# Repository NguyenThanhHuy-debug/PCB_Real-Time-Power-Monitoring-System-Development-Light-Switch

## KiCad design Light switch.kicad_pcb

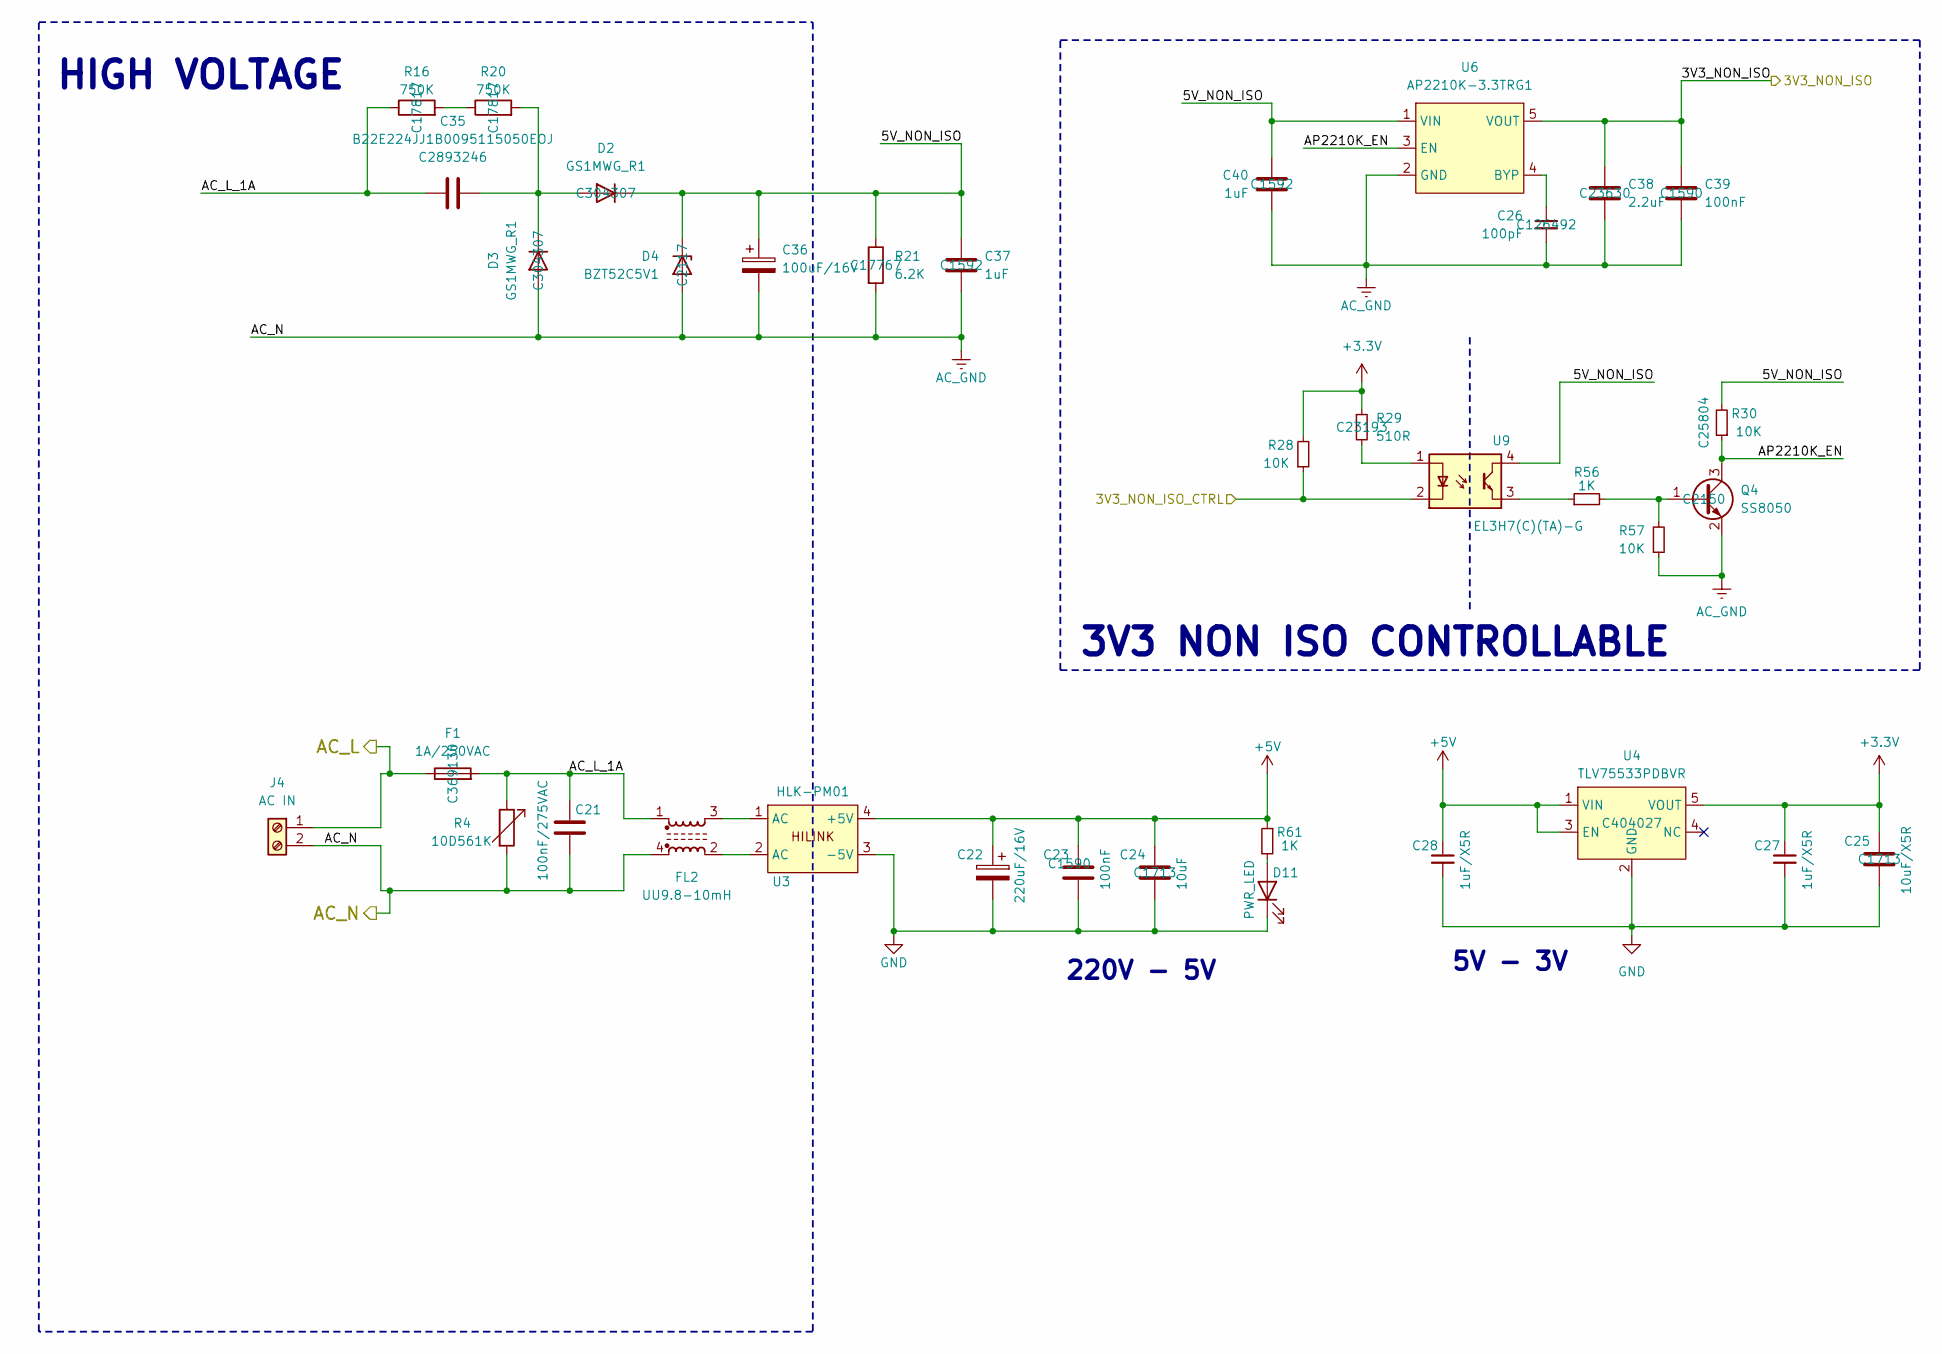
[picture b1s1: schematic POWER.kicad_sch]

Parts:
C21: 100nF/275VAC; C_Rect_L13.0mm_W6.0mm_P10.00mm_FKS3_FKP3_MKS4; JLC C489079
C22: 220uF/16V; C_Elec_6.3x7.7; JLC C3342
C23, C39: 100nF; C_0603_1608Metric; JLC C1590
C24: 10uF; C_0805_2012Metric; JLC C1713
C25: 10uF/X5R; C_0805_2012Metric; JLC C1713
C26: 100pF; C_0402_1005Metric; JLC C126492
C27, C28: 1uF/X5R; C_0603_1608Metric; JLC C15849
C35: B22E224JJ1B0095115050EOJ; C_Rect_L9.0mm_W5.1mm_P7.50mm_MKT; JLC C2893246
C36: 100uF/16V; CP_Radial_D5.0mm_P2.00mm; JLC C43803
C37, C40: 1uF; C_0603_1608Metric; JLC C1592
C38: 2.2uF; C_0603_1608Metric; JLC C23630
D2, D3: GS1MWG_R1; D_SMA; JLC C304307
D4: BZT52C5V1; D_SOD-123; JLC C2117
D11: PWR_LED; LED_0603_1608Metric; JLC C2286
F1: 1A/250VAC; JK250-120U_C369130; JLC C369130
FL2: UU9.8-10mH; JLC C148474
J4: AC IN; TerminalBlock_P5.00mm; JLC C3703
Q4: SS8050; SOT-23; JLC C2150
R4: 10D561K; MOV-10D561K_BRN; JLC C233178
R16, R20: 750K; R_0805_2012Metric; JLC C17817
R21: 6.2K; R_0805_2012Metric; JLC C17767
R28, R30, R57: 10K; R_0603_1608Metric; JLC C25804
R29: 510R; R_0603_1608Metric; JLC C23193
R56, R61: 1K; R_0603_1608Metric; JLC C21190
U3: HLK-PM01; CONV_HLK-PM01; JLC C209903
U4: TLV75533PDBVR; SOT-23-5; JLC C404027
U6: AP2210K-3.3TRG1; SOT-23-5; JLC C155508
U9: EL3H7(C)(TA)-G; SSOP-4_4.4x2.6mm_P1.27mm; JLC C92243

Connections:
+3.3V: C25.1, C27.1, R28.2, R29.1, U4.5 (VOUT); also elsewhere on the board
+5V: C22.1, C23.1, C24.1, C28.1, R61.1, U3.4 (+5V), U4.1 (VIN), U4.3 (EN); also elsewhere on the board
/AC_Peripheral/3V3_NON_ISO: C38.1, C39.1, U6.5 (VOUT); also elsewhere on the board
/AC_Peripheral/AC_L: F1.1, J4.1; also elsewhere on the board
/MCU/3V3_NON_ISO_CTRL: R28.1, U9.2 (K); also elsewhere on the board
/POWER/5V_NON_ISO: C36.1, C37.1, C40.1, D2.1 (K), D4.1 (K), R21.1, R30.2, U6.1 (VIN), U9.4 (E)
/POWER/AC_L_1A: C21.1, C35.1, F1.2, FL2.1, R4.1, R16.1
/POWER/AP2210K_EN: Q4.3 (C), R30.1, U6.3 (EN)
AC_GND: C21.2, C26.2, C36.2, C37.2, C38.2, C39.2, C40.2, D3.2 (A), D4.2 (A), FL2.4, J4.2, Q4.2 (E), R4.2, R21.2, R57.1, U6.2 (GND); also elsewhere on the board
GND: C22.2, C23.2, C24.2, C25.2, C27.2, C28.2, D11.1 (K), U3.3 (-5V), U4.2 (GND); also elsewhere on the board
unnamed: C35.2, D2.2 (A), D3.1 (K), R20.2
unnamed: D11.2 (A), R61.2
unnamed: FL2.2, U3.2 (AC)
unnamed: FL2.3, U3.1 (AC)
unnamed: Q4.1 (B), R56.2, R57.2
unnamed: R16.2, R20.1
unnamed: C26.1, U6.4 (BYP)
unnamed: R29.2, U9.1 (A)
unnamed: R56.1, U9.3 (C)

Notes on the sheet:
220V - 5V
3V3 NON ISO CONTROLLABLE
HIGH VOLTAGE
5V - 3V

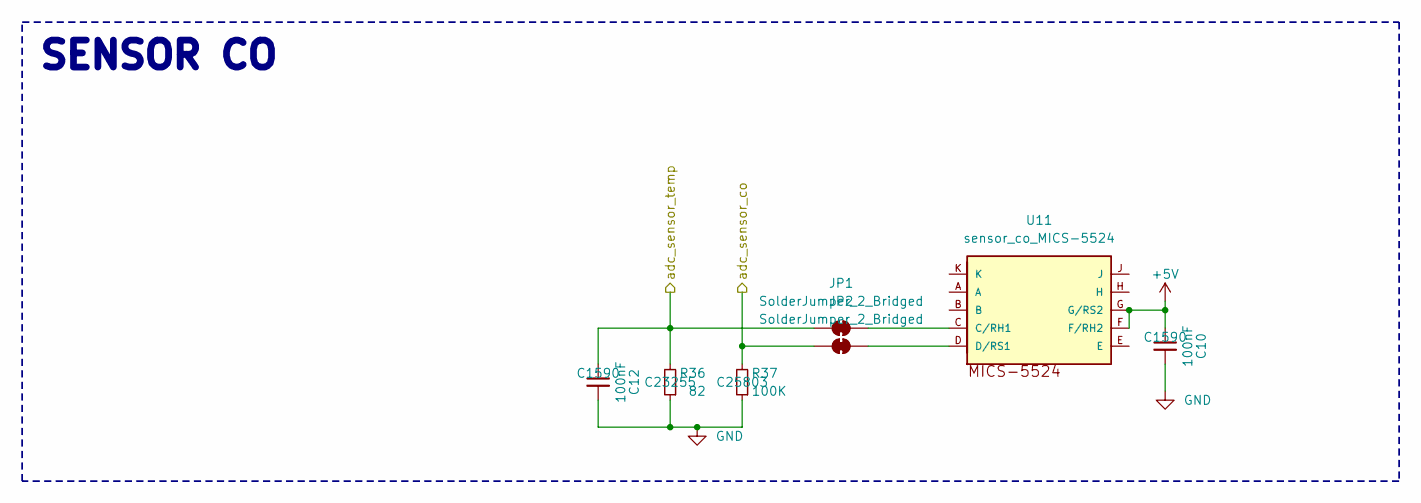
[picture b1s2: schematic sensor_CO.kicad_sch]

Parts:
C10, C12: 100nF; C_0603_1608Metric; JLC C1590
JP1, JP2: SolderJumper_2_Bridged; SolderJumper-2_P1.3mm_Bridged_RoundedPad1.0x1.5mm
R36: 82; R_0603_1608Metric; JLC C23255
R37: 100K; R_0603_1608Metric; JLC C25803
U11: sensor_co_MICS-5524; MICS-SMD10; JLC C3659348

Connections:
+5V: C10.1, U11.F (F/RH2), U11.G (G/RS2); also elsewhere on the board
/MCU/ADC1_INT10: JP2.1 (A), R37.2; also elsewhere on the board
/MCU/ADC1_INT11: C12.1, JP1.1 (A), R36.2; also elsewhere on the board
GND: C10.2, C12.2, R36.1, R37.1; also elsewhere on the board
unnamed: JP1.2 (B), U11.C (C/RH1)
unnamed: JP2.2 (B), U11.D (D/RS1)

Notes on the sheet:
SENSOR CO

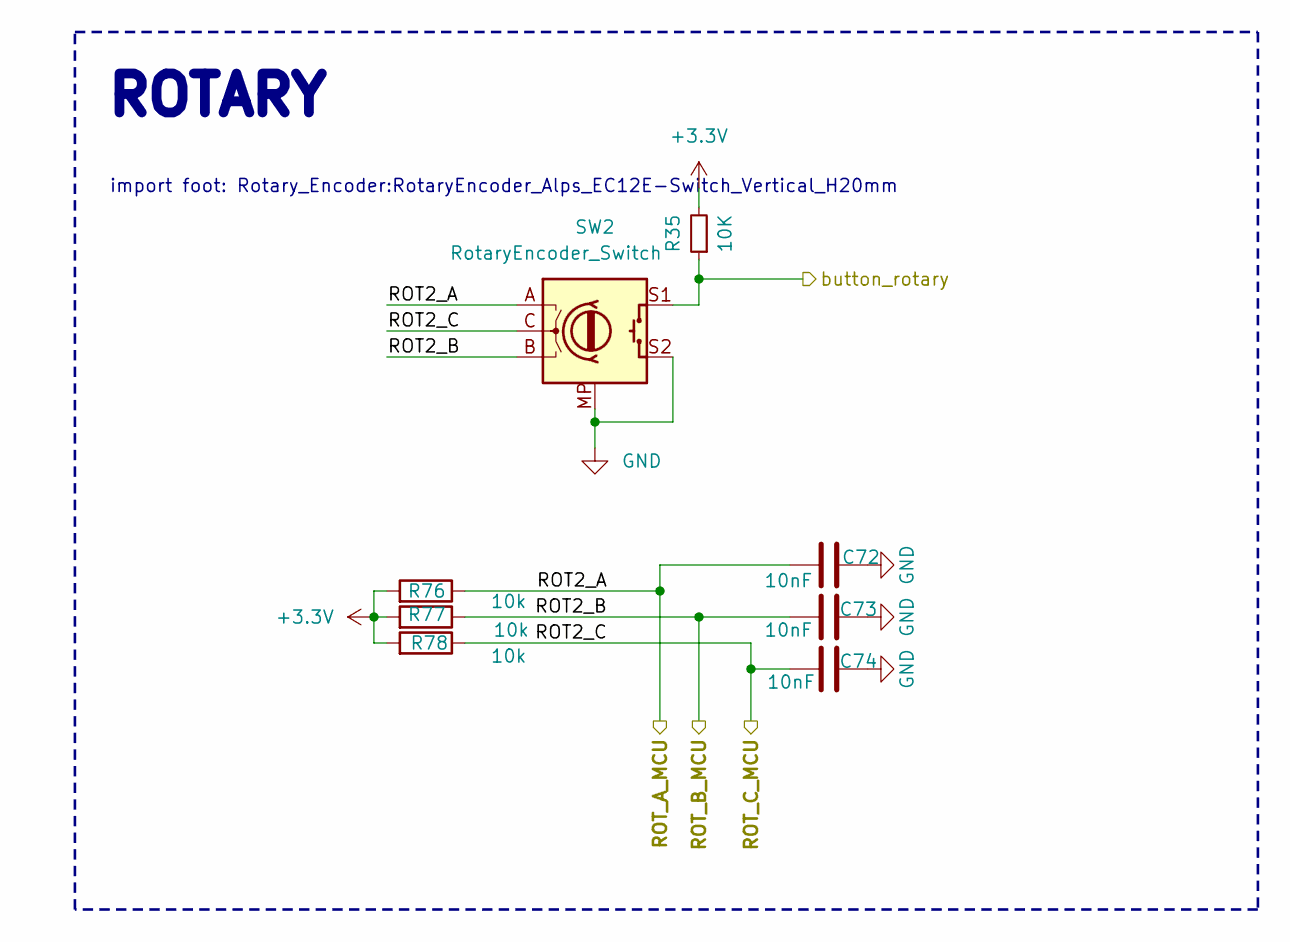
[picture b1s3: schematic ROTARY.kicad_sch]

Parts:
C72, C73, C74: 10nF; C_0402_1005Metric; JLCPCB C60133
R35: 10K; R_0603_1608Metric
R76, R77, R78: 10k; R_0402_1005Metric; JLCPCB C25531
SW2: RotaryEncoder_Switch; RotaryEncoder; JLC C398934

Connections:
+3.3V: R35.2, R76.2, R77.2, R78.2; also elsewhere on the board
/MCU/rotary_mcu: R35.1, SW2.S1; also elsewhere on the board
/ROTARY/ROT2_A: C72.1, R76.1, SW2.A; also elsewhere on the board
/ROTARY/ROT2_B: C73.1, R77.1, SW2.B; also elsewhere on the board
/ROTARY/ROT2_C: C74.1, R78.1, SW2.C; also elsewhere on the board
GND: C72.2, C73.2, C74.2, SW2.MP (Shield), SW2.S2; also elsewhere on the board

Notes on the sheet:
import foot: Rotary_Encoder:RotaryEncoder_Alps_EC12E-Switch_Vertical_H20mm
ROTARY

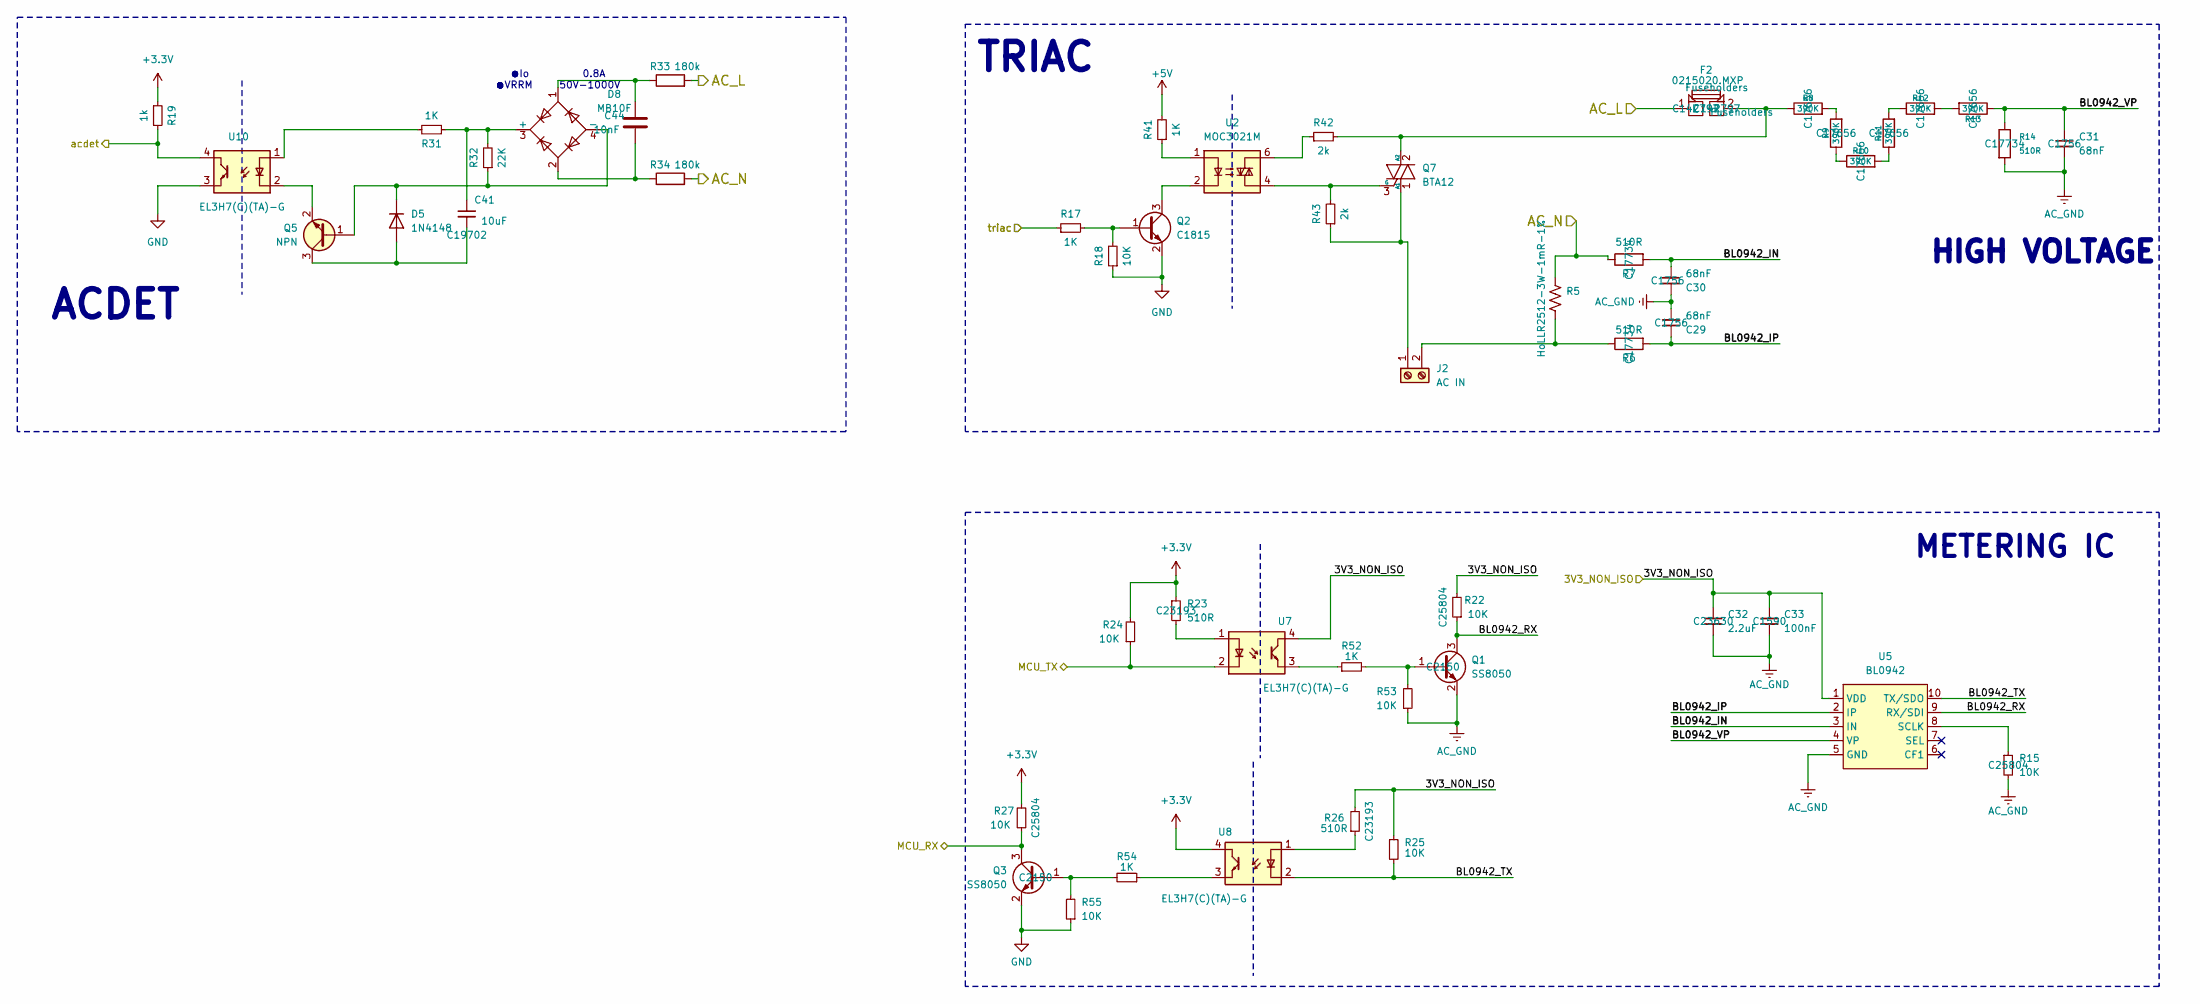
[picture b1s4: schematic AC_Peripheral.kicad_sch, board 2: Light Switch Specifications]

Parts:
C29, C30, C31: 68nF; C_0805_2012Metric; JLC C1756
C32: 2.2uF; C_0603_1608Metric; JLC C23630
C33: 100nF; C_0603_1608Metric; JLC C1590
C41: 10uF; C_0603_1608Metric; JLC C19702
C44: 10nF; C_0805_2012Metric_Pad1.18x1.45mm_HandSolder; JLC C1710
D5: 1N4148; Nexperia_CFP3_SOD-123W; JLC C2099
D8: MB10F; Diode_Bridge_Vishay_MBLS; JLC C108823
F2: 0215020.MXP; JLC C3166374
FH1: Fuseholders; FUSE_L; JLC C142797
FH2: Fuseholders; FUSE_R; JLC C142797
J2: AC IN; TerminalBlock_P5.00mm; JLC C3703
Q1, Q3: SS8050; SOT-23; JLC C2150
Q2: C1815; SOT-23-3
Q5: NPN; TSOT-23; JLC C81464
Q7: BTA12; TO-220-3_Vertical; JLC C253902
R5: HoLLR2512-3W-1mR-1%; R_2512_6332Metric; JLC C2994638
R6, R7, R14: 510R; R_0805_2012Metric; JLC C17734
R8, R9, R10, R11, R12, R13: 390K; R_0805_2012Metric; JLC C17656
R15, R22, R24, R25, R27, R53, R55: 10K; R_0603_1608Metric; JLC C25804
R17, R41: 1K; R_0603_1608Metric
R18: 10K; R_0603_1608Metric
R19: 1k; R_0603_1608Metric; JLC C21190
R23, R26: 510R; R_0603_1608Metric; JLC C23193
R31, R52, R54: 1K; R_0603_1608Metric; JLC C21190
R32: 22K; R_0603_1608Metric; JLC C31850
R33, R34: 180k; R_0805_2012Metric_Pad1.20x1.40mm_HandSolder; JLC C17501
R42, R43: 2k; R_0603_1608Metric; JLC C21190
U2: MOC3021M; moc3021_120V; JLC C108500
U5: BL0942; SSOP-10_3.9x4.9mm_P1.00mm; JLC C2837510
U7, U8, U10: EL3H7(C)(TA)-G; SSOP-4_4.4x2.6mm_P1.27mm; JLC C92243

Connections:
+3.3V: R19.1, R23.1, R24.2, R27.2, U8.4 (E); also elsewhere on the board
+5V: R41.2; also elsewhere on the board
/AC_Peripheral/3V3_NON_ISO: C32.1, C33.1, R22.2, R25.1, R26.2, U5.1 (VDD), U7.4 (E); also elsewhere on the board
/AC_Peripheral/AC_L: FH1.1 (L), R33.2; also elsewhere on the board
/AC_Peripheral/BL0942_IN: C30.2, R7.2, U5.3 (IN)
/AC_Peripheral/BL0942_IP: C29.1, R6.2, U5.2 (IP)
/AC_Peripheral/BL0942_RX: Q1.3 (C), R22.1, U5.9 (RX/SDI)
/AC_Peripheral/BL0942_TX: R25.2, U5.10 (TX/SDO), U8.2 (K)
/AC_Peripheral/BL0942_VP: C31.1, R13.1, R14.1, U5.4 (VP)
/AC_Peripheral/MCU_RX: Q3.3 (C), R27.1; also elsewhere on the board
/AC_Peripheral/MCU_TX: R24.1, U7.2 (K); also elsewhere on the board
/AC_Peripheral/acdet: R19.2, U10.4 (E); also elsewhere on the board
/AC_Peripheral/triac: R17.1; also elsewhere on the board
AC_GND: C29.2, C30.1, C31.2, C32.2, C33.2, Q1.2 (E), R5.1, R7.1, R14.2, R15.2, R34.2, R53.1, U5.5 (GND); also elsewhere on the board
GND: Q2.2 (E), Q3.2 (E), R18.1, R55.1, U10.3 (C); also elsewhere on the board
unnamed: C44.1, D8.1, R33.1
unnamed: C44.2, D8.2, R34.1
unnamed: C41.2, D5.2 (A), Q5.3 (C)
unnamed: D5.1 (K), D8.4 (-), Q5.1 (B), R32.1
unnamed: C41.1, D8.3 (+), R31.1, R32.2
unnamed: FH2.2 (R), Q7.2 (A2), R8.1, R42.2
unnamed: J2.1, Q7.1 (A1), R43.1
unnamed: J2.2, R5.2, R6.1
unnamed: Q1.1 (B), R52.2, R53.2
unnamed: Q2.1 (B), R17.2, R18.2
unnamed: Q2.3 (C), U2.2
unnamed: Q3.1 (B), R54.2, R55.2
unnamed: Q5.2 (E), U10.2 (K)
unnamed: Q7.3 (G), R43.2, U2.4
unnamed: R8.2, R9.2
unnamed: R9.1, R10.1
unnamed: R10.2, R11.1
unnamed: R11.2, R12.1
unnamed: R12.2, R13.2
unnamed: R41.1, U2.1
unnamed: R42.1, U2.6
unnamed: R15.1, U5.8 (SCLK)
unnamed: R23.2, U7.1 (A)
unnamed: R52.1, U7.3 (C)
unnamed: R26.1, U8.1 (A)
unnamed: R54.1, U8.3 (C)
unnamed: R31.2, U10.1 (A)

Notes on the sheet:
●Io 0.8A ●VRRM 50V-1000V
HIGH VOLTAGE
ACDET
METERING IC
TRIAC

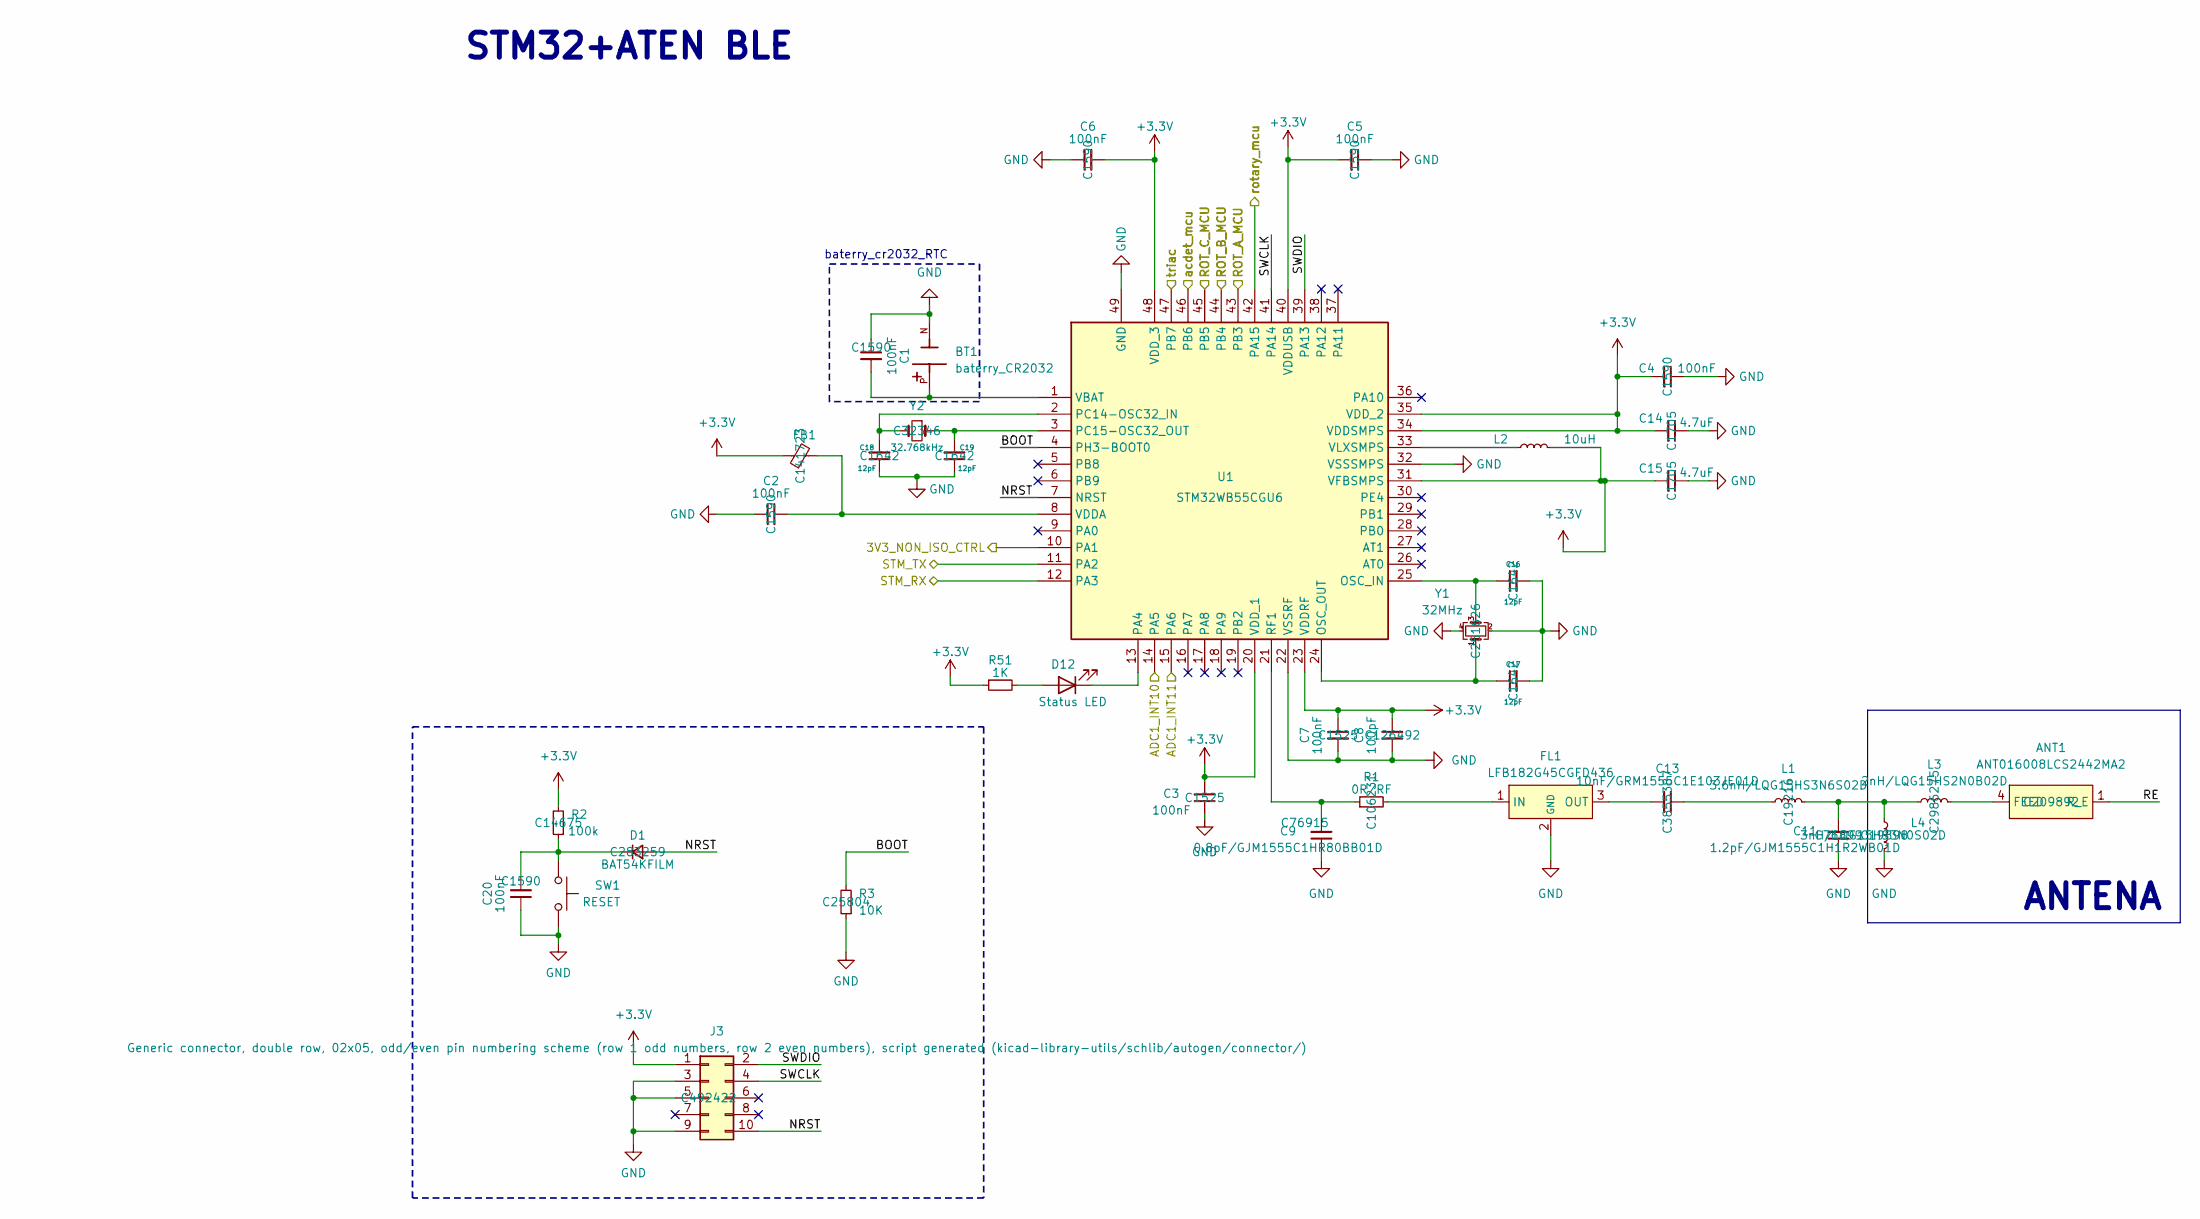
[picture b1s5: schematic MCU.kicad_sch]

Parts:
ANT1: ANT016008LCS2442MA2; QFN_2442MA2_TDK_1; JLC C209892
BT1: baterry_CR2032; baterry_cr2032; PARTREV 3; JLC C70377
C1, C2, C4, C5, C6, C20: 100nF; C_0603_1608Metric; JLC C1590
C3, C7: 100nF; C_0402_1005Metric; JLC C1525
C8: 100pF; C_0402_1005Metric; JLC C126492
C9: 0.8pF/GJM1555C1HR80BB01D; C_0402_1005Metric; JLC C76915
C11: 1.2pF/GJM1555C1H1R2WB01D; C_0402_1005Metric; JLC C76899
C13: 10nF/GRM1555C1E103JE01D; C_0402_1005Metric; JLC C3855387
C14, C15: 4.7uF; C_0603_1608Metric; JLC C1705
C16, C17, C18, C19: 12pF; C_0603_1608Metric; JLC C1642
D1: BAT54KFILM; D_SOD-523; JLC C283259
D12: Status LED; LED_0603_1608Metric; JLC C19171301
FB1: FCM1608KF-601T03; L_0603_1608Metric; JLC C141723
FL1: LFB182G45CGFD436; JLC C2718492
J3: Connector 2x5; PinHeader_2x05_P2.54mm_Vertical; JLC C492422
L1: 3.6nH/LQG15HS3N6S02D; L_0402_1005Metric; JLC C19216
L2: 10uH; L_0805_2012Metric; JLC C139245
L3: 2nH/LQG15HS2N0B02D; L_0402_1005Metric; JLC C2986275
L4: 3nH/LQG15HS3N0S02D; L_0402_1005Metric; JLC C19898
R1: 0R/RF; R_0402_1005Metric; JLC C106231
R2: 100k; R_0603_1608Metric; JLC C14675
R3: 10K; R_0603_1608Metric; JLC C25804
R51: 1K; R_0603_1608Metric; JLC C21190
SW1: RESET; SW_PUSH_6mm_H13mm; JLC C7528718
U1: STM32WB55CGU6; QFN50P700X700X60-49N-D; Mouser Part Number 511-STM32WB55CGU6
Y1: 32MHz; Crystal_SMD_3225-4Pin_3.2x2.5mm; JLC C251626
Y2: 32.768kHz; Crystal_SMD_3215-2Pin_3.2x1.5mm; JLC C32346

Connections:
+3.3V: C3.2, C4.2, C5.2, C6.2, C7.1, C8.1, C14.2, C15.2, FB1.1, J3.1, L2.2, R2.2, R51.1, U1.20 (VDD_1), U1.23 (VDDRF), U1.31 (VFBSMPS), U1.34 (VDDSMPS), U1.35 (VDD_2), U1.40 (VDDUSB), U1.48 (VDD_3); also elsewhere on the board
/AC_Peripheral/MCU_RX: U1.12 (PA3); also elsewhere on the board
/AC_Peripheral/MCU_TX: U1.11 (PA2); also elsewhere on the board
/AC_Peripheral/acdet: U1.46 (PB6); also elsewhere on the board
/AC_Peripheral/triac: U1.47 (PB7); also elsewhere on the board
/MCU/3V3_NON_ISO_CTRL: U1.10 (PA1); also elsewhere on the board
/MCU/ADC1_INT10: U1.14 (PA5); also elsewhere on the board
/MCU/ADC1_INT11: U1.15 (PA6); also elsewhere on the board
/MCU/BOOT: R3.2, U1.4 (PH3-BOOT0)
/MCU/NRST: D1.2 (A), J3.10, U1.7 (NRST)
/MCU/RE: ANT1.1 (R_E)
/MCU/SWCLK: J3.4, U1.41 (PA14)
/MCU/SWDIO: J3.2, U1.39 (PA13)
/MCU/rotary_mcu: U1.42 (PA15); also elsewhere on the board
/ROTARY/ROT2_A: U1.43 (PB3); also elsewhere on the board
/ROTARY/ROT2_B: U1.44 (PB4); also elsewhere on the board
/ROTARY/ROT2_C: U1.45 (PB5); also elsewhere on the board
GND: BT1.N, C1.1, C2.1, C3.1, C4.1, C5.1, C6.1, C7.2, C8.2, C9.1, C11.1, C14.1, C15.1, C16.2, C17.2, C18.1, C19.1, C20.1, FL1.2 (GND), J3.3, J3.5, J3.9, L4.1, R3.1, SW1.1, U1.22 (VSSRF), U1.32 (VSSSMPS), U1.49 (GND), Y1.2, Y1.4; also elsewhere on the board
unnamed: ANT1.4 (FEED), L3.2
unnamed: C11.2, L1.2, L3.1, L4.2
unnamed: C13.1, L1.1
unnamed: C20.2, D1.1 (K), R2.1, SW1.2
unnamed: D12.2 (A), R51.2
unnamed: D12.1 (K), U1.13 (PA4)
unnamed: FL1.1 (IN), R1.2
unnamed: C13.2, FL1.3 (OUT)
unnamed: C16.1, U1.25 (OSC_IN), Y1.3
unnamed: C17.1, U1.24 (OSC_OUT), Y1.1
unnamed: C18.2, U1.2 (PC14-OSC32_IN), Y2.2
unnamed: C19.2, U1.3 (PC15-OSC32_OUT), Y2.1
unnamed: C9.2, R1.1, U1.21 (RF1)
unnamed: BT1.P, C1.2, U1.1 (VBAT)
unnamed: C2.2, FB1.2, U1.8 (VDDA)
unnamed: L2.1, U1.33 (VLXSMPS)

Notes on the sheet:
STM32+ATEN BLE
ANTENA
baterry_cr2032_RTC

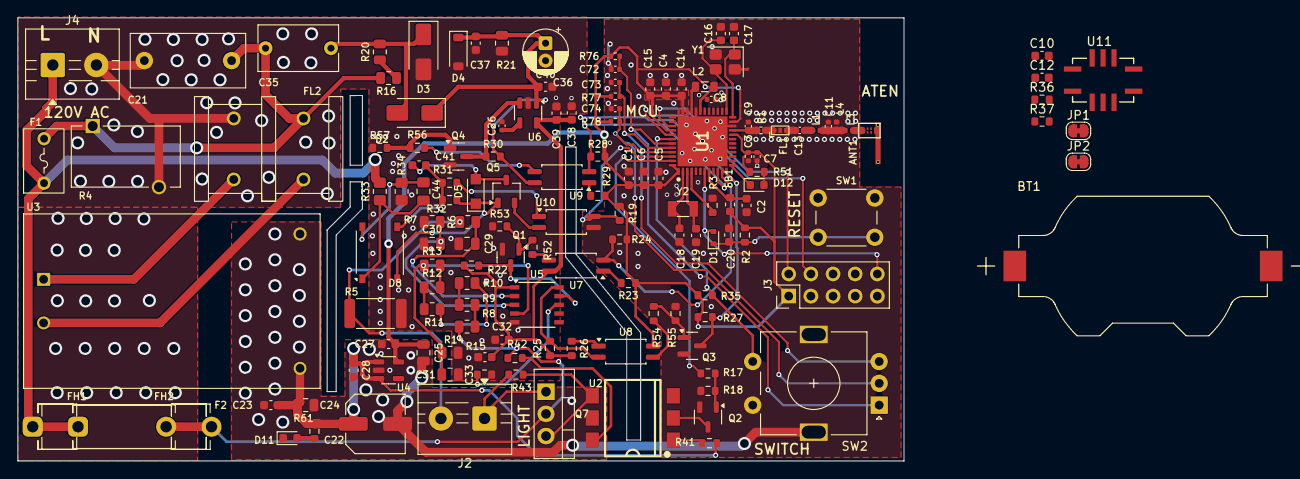
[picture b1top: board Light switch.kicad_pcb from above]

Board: 2 copper layers, 101.6 x 50.8 mm, 142 parts (0 on the bottom side), 83 nets.
